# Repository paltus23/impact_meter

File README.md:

## Device Description

* The accelerometer board is based on the ESP32-C3FH4 microcontroller and the ADXL375 accelerometer.
* The device can be powered either from a battery or via USB. When USB is connected, the battery is automaticly disconnected over MOSFET.
* The USB port is connected using wires. It is used to power the device, flash firmware, and perform debugging.
* A spare UART port is available for firmware flashing and debugging.
* Several additional GPIOs are brought out to test points for possible future use.
* Communication is performed via Wi-Fi.
* Recording and transmission of data are intended to be carried out at different times (not simultaneously).

## Impact meter v1
There is few photos of ready device

## v1 known issues
3.3 V power supply do not connected to ESP32

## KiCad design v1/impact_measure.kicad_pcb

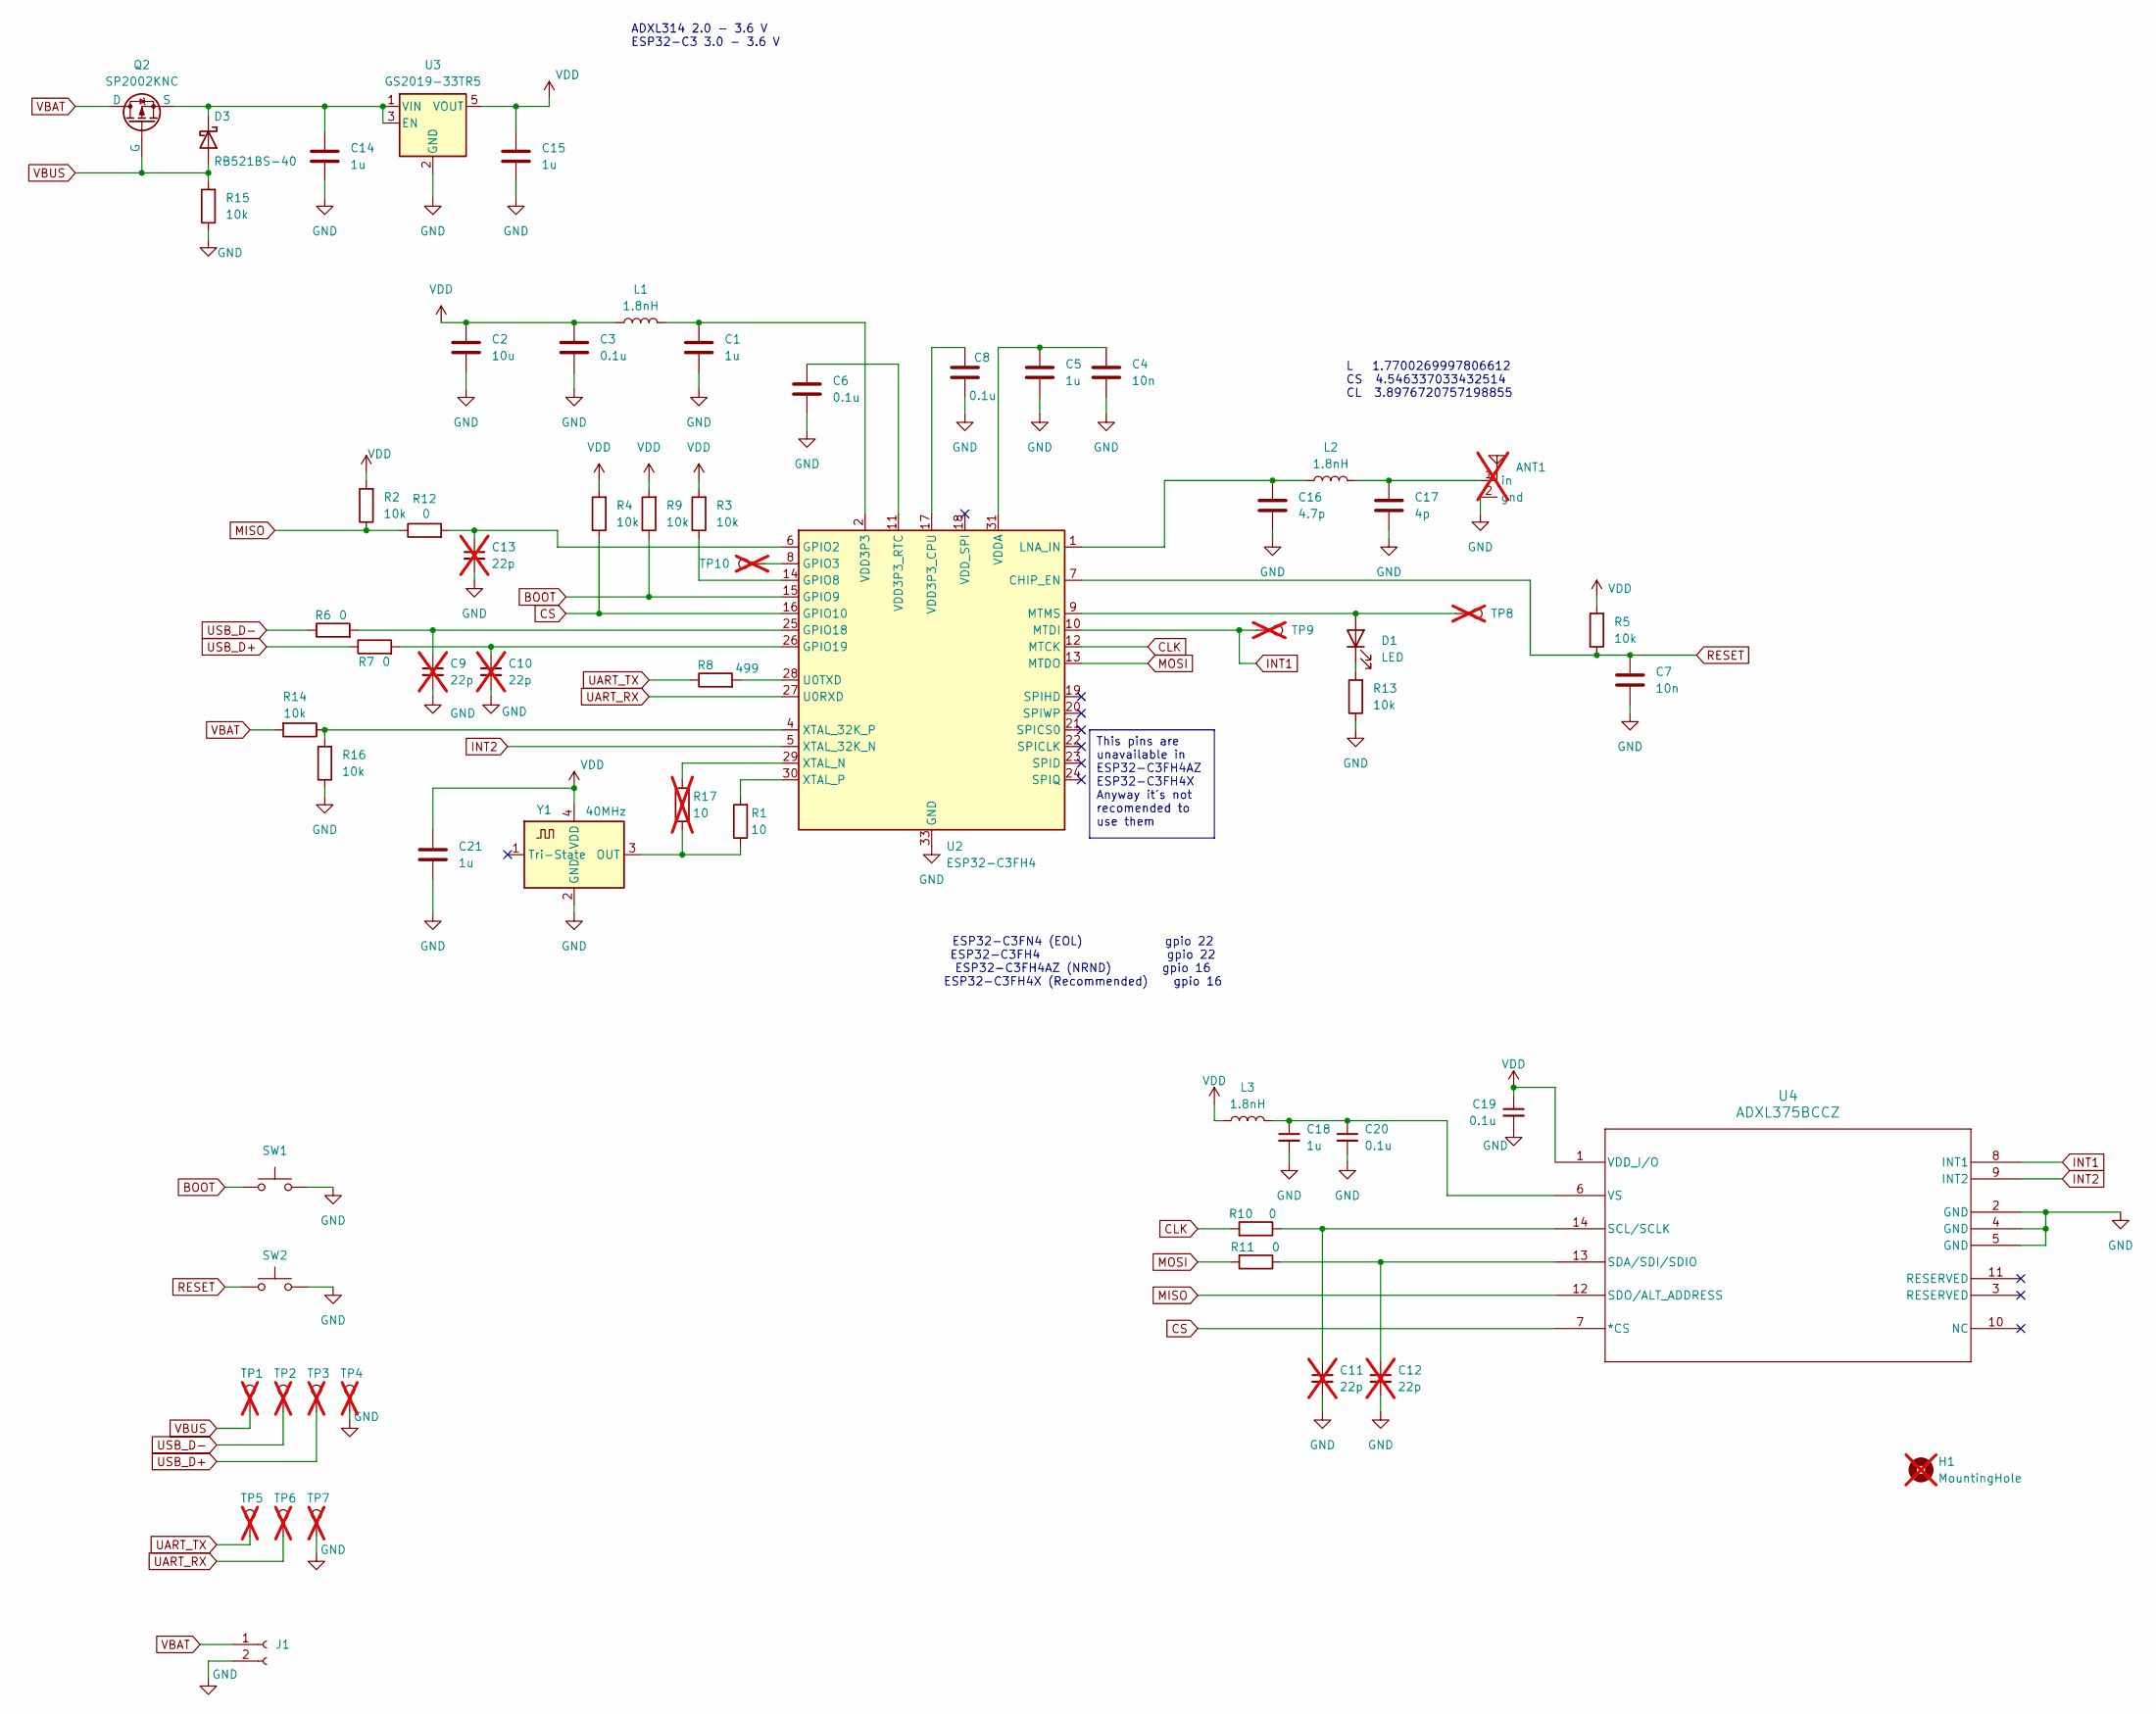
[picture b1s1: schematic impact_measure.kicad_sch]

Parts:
ANT1: 2_4GHz_AN043; not fitted
C1, C5, C14, C15, C18, C21: 1u; C_0402_1005Metric; PartNumber CC0402KRX5R6BB105; LCSC C106254
C2: 10u; C_0603_1608Metric; PartNumber CC0402KRX5R6BB105; LCSC C109453
C3, C6, C8, C19, C20: 0.1u; C_0402_1005Metric; PartNumber CC0402KRX7R7BB104; LCSC C60474
C4, C7: 10n; C_0402_1005Metric; PartNumber CC0402MRX7R6BB103; LCSC C527020
C9, C10, C11, C12, C13: 22p; C_0402_1005Metric; PartNumber CC0402JRNPO8BN220; LCSC C541361; not fitted
C16: 4.7p; C_0402_1005Metric; PartNumber CGA0402C0G4R7C500GT; LCSC C20069279
C17: 4p; C_0402_1005Metric; PartNumber CSA0402C0G4R0C500GT; LCSC C48642896
D1: LED; LED_0402_1005Metric; PartNumber GL0402YG01; LCSC C51933305
D3: RB521BS-40; D_SOD-882; PartNumber RB521BS-40; LCSC C53207092
H1: MountingHole; MountingHole_3.2mm_M3; not fitted
J1: Bossie BX-MX1.25-2PWT; mx1.25; LCSC C18077932
L1, L2, L3: 1.8nH; L_0402_1005Metric; PartNumber VHF100505HQ1N8ST; LCSC C395057
Q2: SP2002KNC; Diodes_DFN1006-3; PartNumber SP2002KNC; LCSC C41354895
R1: 10; R_0402_1005Metric; PartNumber RC0402FR-0710RL; LCSC C138066
R2, R3, R4, R5, R9, R13, R14, R15, R16: 10k; R_0402_1005Metric; PartNumber RC0402FR-0710KL; LCSC C60490
R6, R7, R10, R11, R12: 0; R_0402_1005Metric; PartNumber RC0402FR-070RL; LCSC C106231
R8: 499; R_0402_1005Metric; PartNumber RC0402FR-07499RL; LCSC C137970
R17: 10; R_0402_1005Metric; not fitted
SW1, SW2: SW_Push; SW_Push_SPST_NO_Alps_SKRK; PartNumber TS-1088-AR02016; LCSC C720477
TP1, TP2, TP3, TP4, TP5, TP6, TP7, TP8, TP9, TP10: TestPoint; TP_1x2mm; not fitted
U2: ESP32-C3FH4; QFN-32-1EP_5x5mm_P0.5mm_EP3.7x3.7mm; PartNumber ESP32-C3FH4; LCSC C2858491
U3: GS2019-33TR5; SOT-23-5; PartNumber GS2019-33TR5; LCSC C41419378
U4: ADXL375BCCZ; LGA_CC-14-1_ADXL375; PartNumber ADXL375BCCZ; LCSC C579466
Y1: 40MHz; Oscillator_SMD_Abracon_ASE-4Pin_3.2x2.5mm; PartNumber OW2EL89CENUXK7YLC-40M; LCSC C48888233

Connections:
BOOT: R9.1, SW1.1, U2.15 (GPIO9)
CLK: R10.2, U2.12 (MTCK)
CS: R4.1, U2.16 (GPIO10), U4.7 (*CS)
GND: ANT1.2 (gnd), C1.2, C2.2, C3.2, C4.2, C5.2, C6.2, C7.2, C8.2, C9.2, C10.2, C11.2, C12.2, C13.2, C14.2, C15.2, C16.2, C17.2, C18.2, C19.2, C20.2, C21.2, J1.2, R13.1, R15.1, R16.1, SW1.2, SW2.2, TP4.1, TP7.1, U2.33 (GND), U3.2 (GND), U4.2 (GND), U4.4 (GND), U4.5 (GND), Y1.2 (GND)
INT1: TP9.1, U2.10 (MTDI), U4.8 (INT1)
INT2: U2.5 (XTAL_32K_N), U4.9 (INT2)
MISO: R2.1, R12.1, U4.12 (SDO/ALT_ADDRESS)
MOSI: R11.2, U2.13 (MTDO)
unnamed: ANT1.1 (in), C17.1, L2.2
unnamed: C1.1, L1.2, U2.2 (VDD3P3), U2.3 (VDD3P3)
unnamed: C4.1, C5.1, U2.31 (VDDA), U2.32 (VDDA)
unnamed: D1.2 (A), TP8.1, U2.9 (MTMS)
unnamed: D1.1 (K), R13.2
unnamed: C14.1, D3.1 (K), Q2.2 (S), U3.1 (VIN), U3.3 (EN)
unnamed: C13.1, R12.2, U2.6 (GPIO2)
unnamed: TP10.1, U2.8 (GPIO3)
unnamed: R3.1, U2.14 (GPIO8)
unnamed: C9.1, R6.2, U2.25 (GPIO18)
unnamed: C10.1, R7.2, U2.26 (GPIO19)
unnamed: C16.1, L2.1, U2.1 (LNA_IN)
unnamed: R8.2, U2.28 (U0TXD)
unnamed: C8.1, U2.17 (VDD3P3_CPU)
unnamed: C6.1, U2.11 (VDD3P3_RTC)
unnamed: R14.1, R16.2, U2.4 (XTAL_32K_P)
unnamed: R17.2, U2.29 (XTAL_N)
unnamed: R1.2, U2.30 (XTAL_P)
unnamed: C11.1, R10.1, U4.14 (SCL/SCLK)
unnamed: C12.1, R11.1, U4.13 (SDA/SDI/SDIO)
unnamed: C18.1, C20.1, L3.2, U4.6 (VS)
unnamed: R1.1, R17.1, Y1.3 (OUT)
RESET: C7.1, R5.1, SW2.1, U2.7 (CHIP_EN)
UART_RX: TP6.1, U2.27 (U0RXD)
UART_TX: R8.1, TP5.1
USB_D+: R7.1, TP3.1
USB_D-: R6.1, TP2.1
VBAT: J1.1, Q2.3 (D), R14.2
VBUS: D3.2 (A), Q2.1 (G), R15.2, TP1.1
VDD: C2.1, C3.1, C15.1, C19.1, C21.1, L1.1, L3.1, R2.2, R3.2, R4.2, R5.2, R9.2, U3.5 (VOUT), U4.1 (VDD_I/O), Y1.4 (VDD)

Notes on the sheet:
ESP32-C3FN4 (EOL) gpio 22 ESP32-C3FH4 gpio 22 ESP32-C3FH4AZ (NRND) gpio 16 ESP32-C3FH4X (Recommended) gpio 16
L 1.7700269997806612 CS 4.546337033432514 CL 3.8976720757198855
ADXL314 2.0 - 3.6 V ESP32-C3 3.0 - 3.6 V
This pins are unavailable in ESP32-C3FH4AZ ESP32-C3FH4X Anyway it's not recomended to use them

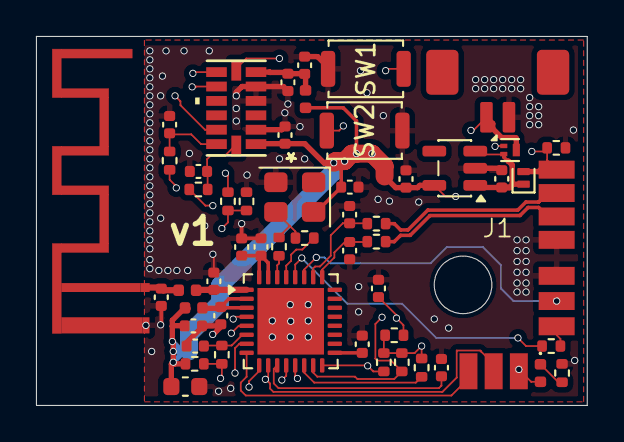
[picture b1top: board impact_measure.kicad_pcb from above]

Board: 4 copper layers, 30.6 x 20.5 mm, 63 parts (0 on the bottom side), 38 nets.

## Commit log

2026-01-24 init commit
2026-01-24 move project to v1 directory
2026-01-24 add README.md
2026-01-28 add decap to Y1 quarz change C2 electrolyte to ceramic add signals int1 and int2
2026-01-29 fixed accel land pattern add via fetching increased m3 keepout diameter add int1 and int2 routes fixed wifi track width to 0,35mm moved 10u decap next to ESP32
2026-01-29 opened mask under screw
2026-01-29 fixed LCSC partnumbers fixed after DRC
2026-01-29 added connector for battery
2026-01-29 added vias for gnd fixed after drc
2026-03-12 add images of ready device of v1
2026-03-12 fixed markup
2026-03-12 fixed markup again
